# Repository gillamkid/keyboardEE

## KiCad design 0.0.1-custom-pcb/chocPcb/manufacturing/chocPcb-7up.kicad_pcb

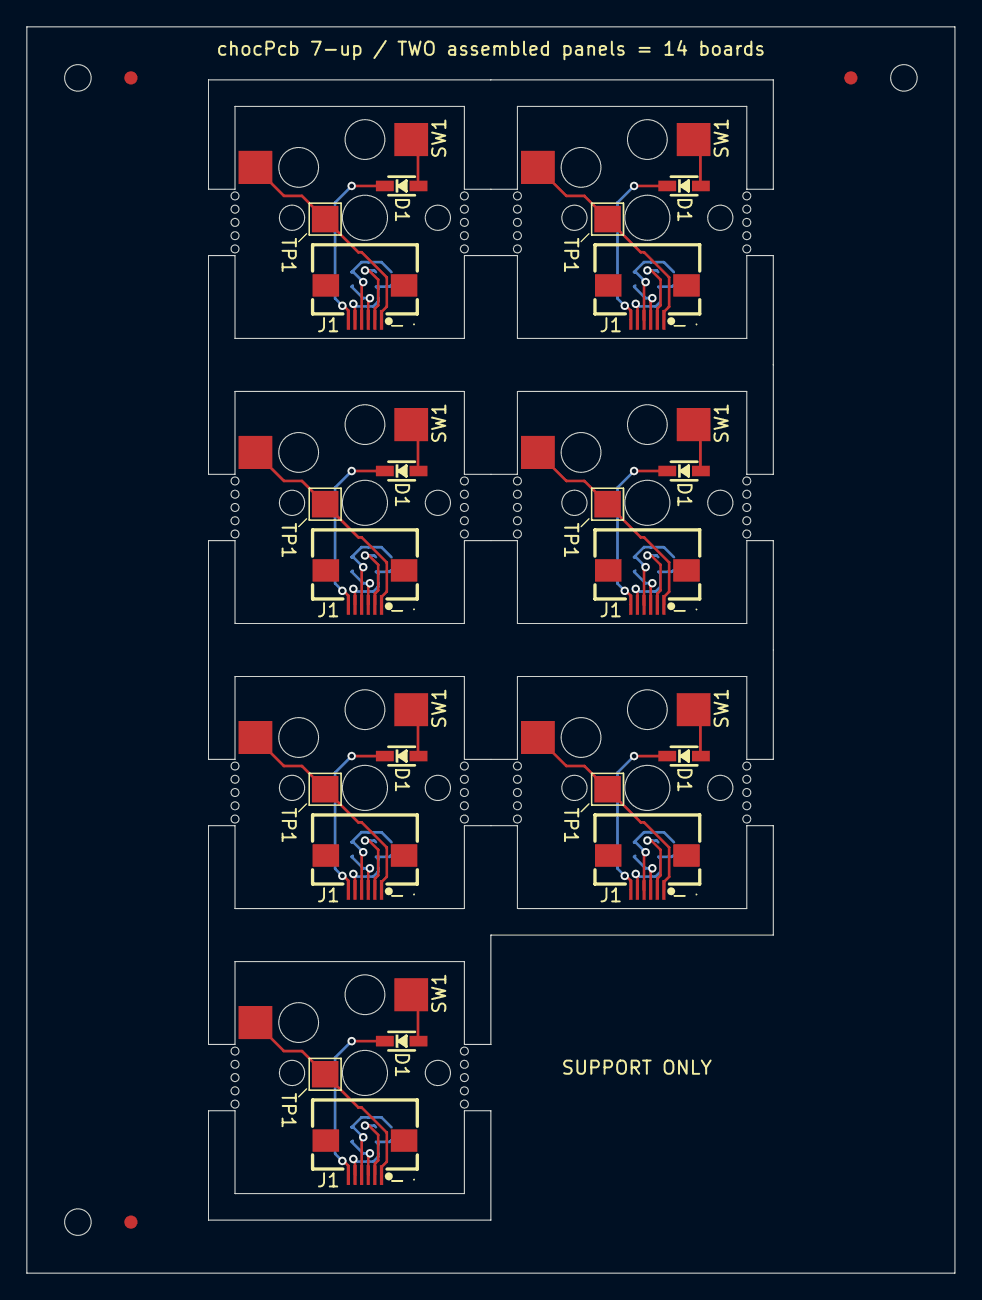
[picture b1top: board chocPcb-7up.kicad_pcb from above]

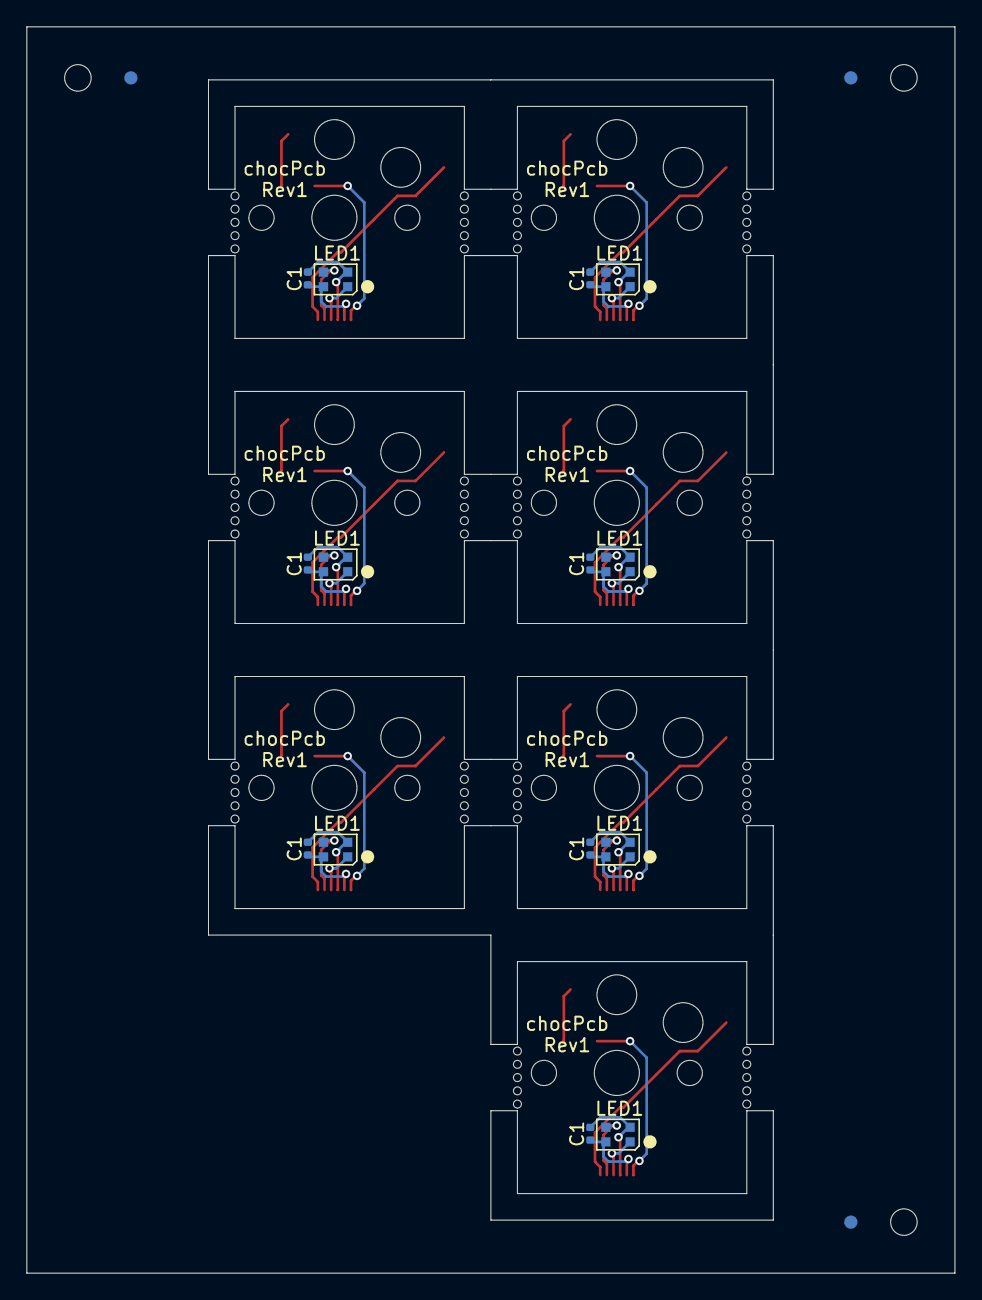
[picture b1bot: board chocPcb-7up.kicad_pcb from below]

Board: 2 copper layers, 70.0 x 94.0 mm, 121 parts (17 on the bottom side), 49 nets.

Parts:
C1_1, C1_2, C1_3, C1_4, C1_5, C1_6, C1_7: 100nF; C_0402_1005Metric
D1_1, D1_2, D1_3, D1_4, D1_5, D1_6, D1_7: 1N4148WS; SOD-323
FIDB1, FIDB2, FIDB3: Fiducial; Fiducial_1mm_B
FIDF1, FIDF2, FIDF3: Fiducial; Fiducial_1mm_F
J1_1, J1_2, J1_3, J1_4, J1_5, J1_6, J1_7: HC-FPC-0.5-6P-FH20; FPC-SMD_6P-P0.50_HC-FPC-0.5-6P-FH20
LED1_1, LED1_2, LED1_3, LED1_4, LED1_5, LED1_6, LED1_7: WS2812B-2020; LED_WS2812B-2020_PLCC4_2.0x2.0mm
MB1L1, MB1L2, MB1L3, MB1L4, MB1L5, MB1R1, MB1R2, MB1R3, MB1R4, MB1R5, MB2L1, MB2L2, MB2L3, MB2L4, MB2L5, MB2R1, MB2R2, MB2R3, MB2R4, MB2R5, MB3L1, MB3L2, MB3L3, MB3L4, MB3L5, MB3R1, MB3R2, MB3R3, MB3R4, MB3R5, MB4L1, MB4L2, MB4L3, MB4L4, MB4L5, MB4R1, MB4R2, MB4R3, MB4R4, MB4R5, MB5L1, MB5L2, MB5L3, MB5L4, MB5L5, MB5R1, MB5R2, MB5R3, MB5R4, MB5R5, MB6L1, MB6L2, MB6L3, MB6L4, MB6L5, MB6R1, MB6R2, MB6R3, MB6R4, MB6R5, MB7L1, MB7L2, MB7L3, MB7L4, MB7L5, MB7R1, MB7R2, MB7R3, MB7R4, MB7R5: NPTH; NPTH_0.6
SW1_1, SW1_2, SW1_3, SW1_4, SW1_5, SW1_6, SW1_7: Kailh Choc socket; KAILH_CHOC_SOCKET
TOOL1, TOOL2, TOOL3: NPTH; NPTH_2.0
TP1_1, TP1_2, TP1_3, TP1_4, TP1_5, TP1_6, TP1_7: TestPoint_Pad_2.0x2.0mm

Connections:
B1/GND: C1_1.2, J1_1.4, LED1_1.2
B1/N$2: D1_1.A, SW1_1.1
B1/NEO_IN: J1_1.2, LED1_1.3
B1/NEO_OUT: J1_1.3, LED1_1.1
B1/SWITCHA: J1_1.1, SW1_1.2, TP1_1.1
B1/SWITCHC: D1_1.C, J1_1.6
B1/VDD: C1_1.1, J1_1.5, LED1_1.4
B2/GND: C1_2.2, J1_2.4, LED1_2.2
B2/N$2: D1_2.A, SW1_2.1
B2/NEO_IN: J1_2.2, LED1_2.3
B2/NEO_OUT: J1_2.3, LED1_2.1
B2/SWITCHA: J1_2.1, SW1_2.2, TP1_2.1
B2/SWITCHC: D1_2.C, J1_2.6
B2/VDD: C1_2.1, J1_2.5, LED1_2.4
B3/GND: C1_3.2, J1_3.4, LED1_3.2
B3/N$2: D1_3.A, SW1_3.1
B3/NEO_IN: J1_3.2, LED1_3.3
B3/NEO_OUT: J1_3.3, LED1_3.1
B3/SWITCHA: J1_3.1, SW1_3.2, TP1_3.1
B3/SWITCHC: D1_3.C, J1_3.6
B3/VDD: C1_3.1, J1_3.5, LED1_3.4
B4/GND: C1_4.2, J1_4.4, LED1_4.2
B4/N$2: D1_4.A, SW1_4.1
B4/NEO_IN: J1_4.2, LED1_4.3
B4/NEO_OUT: J1_4.3, LED1_4.1
B4/SWITCHA: J1_4.1, SW1_4.2, TP1_4.1
B4/SWITCHC: D1_4.C, J1_4.6
B4/VDD: C1_4.1, J1_4.5, LED1_4.4
B5/GND: C1_5.2, J1_5.4, LED1_5.2
B5/N$2: D1_5.A, SW1_5.1
B5/NEO_IN: J1_5.2, LED1_5.3
B5/NEO_OUT: J1_5.3, LED1_5.1
B5/SWITCHA: J1_5.1, SW1_5.2, TP1_5.1
B5/SWITCHC: D1_5.C, J1_5.6
B5/VDD: C1_5.1, J1_5.5, LED1_5.4
B6/GND: C1_6.2, J1_6.4, LED1_6.2
B6/N$2: D1_6.A, SW1_6.1
B6/NEO_IN: J1_6.2, LED1_6.3
B6/NEO_OUT: J1_6.3, LED1_6.1
B6/SWITCHA: J1_6.1, SW1_6.2, TP1_6.1
B6/SWITCHC: D1_6.C, J1_6.6
B6/VDD: C1_6.1, J1_6.5, LED1_6.4
B7/GND: C1_7.2, J1_7.4, LED1_7.2
B7/N$2: D1_7.A, SW1_7.1
B7/NEO_IN: J1_7.2, LED1_7.3
B7/NEO_OUT: J1_7.3, LED1_7.1
B7/SWITCHA: J1_7.1, SW1_7.2, TP1_7.1
B7/SWITCHC: D1_7.C, J1_7.6
B7/VDD: C1_7.1, J1_7.5, LED1_7.4

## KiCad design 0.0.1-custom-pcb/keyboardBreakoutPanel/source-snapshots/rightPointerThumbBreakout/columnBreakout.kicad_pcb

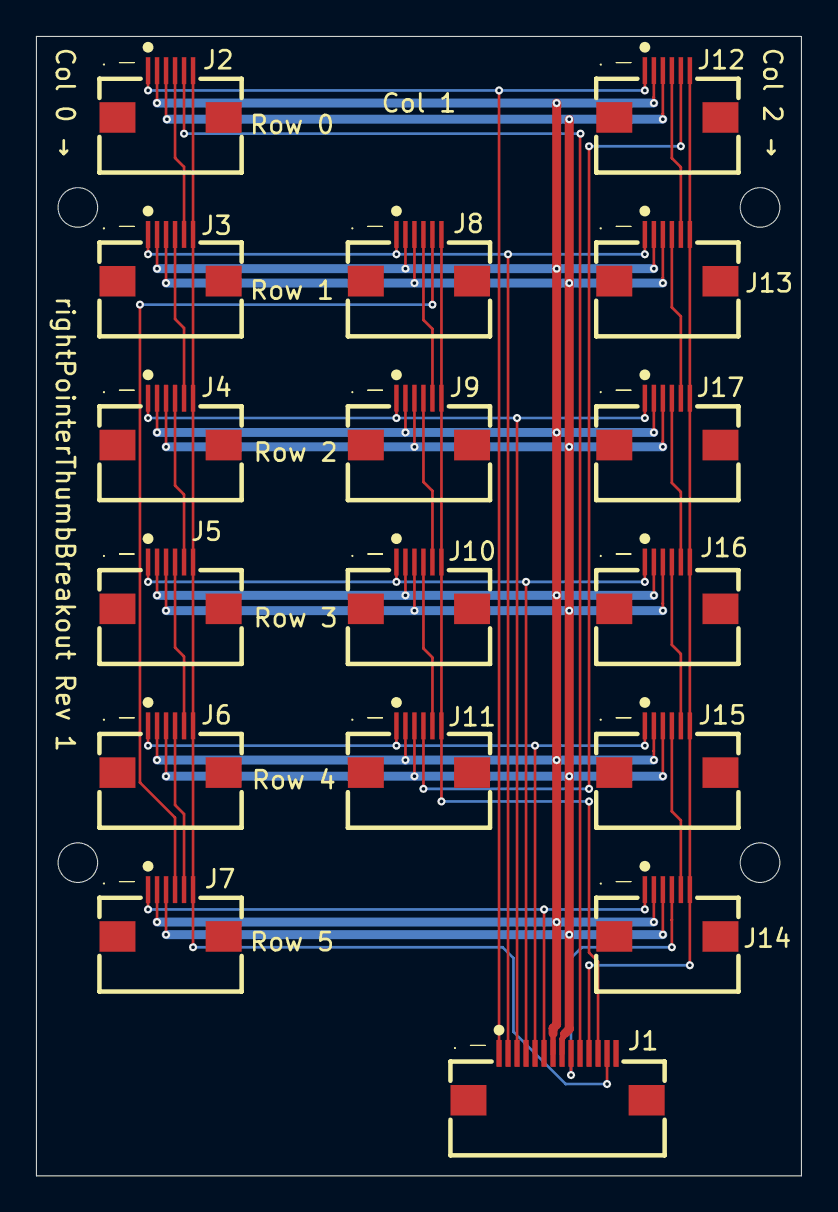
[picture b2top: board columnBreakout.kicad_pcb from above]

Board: 2 copper layers, 42.5 x 63.3 mm, 21 parts (0 on the bottom side), 28 nets.

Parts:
H1, H2, H3, H4: MountingHole_2.2mm_M2_4.4mmHead
J1: HC-FPC-0.5-14P-FH20; FPC-SMD_14P-P0.50_HC-FPC-0.5-14P-FH20
J2, J3, J4, J5, J6, J7, J8, J9, J10, J11, J12, J13, J14, J15, J16, J17: HC-FPC-0.5-6P-FH20; FPC-SMD_6P-P0.50_HC-FPC-0.5-6P-FH20

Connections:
/C0: J1.13, J2.6, J3.6, J4.6, J5.6, J6.6, J7.6
/C1: J1.12, J8.6, J9.6, J10.6, J11.6
/C2: J1.11, J12.6, J13.6, J14.6, J15.6, J16.6, J17.6
/GND: J1.8, J2.3, J3.3, J4.3, J5.3, J6.3, J7.3, J8.3, J9.3, J10.3, J11.3, J12.3, J13.3, J14.3, J15.3, J16.3, J17.3
/IN0: J1.10, J2.5
/IN1: J2.4, J3.5
/IN2: J3.4, J4.5
/IN3: J4.4, J5.5
/IN4: J5.4, J6.5
/IN5: J6.4, J7.5
/IN6: J7.4, J8.5
/IN7: J8.4, J9.5
/IN8: J9.4, J10.5
/IN9: J10.4, J11.5
/IN10: J11.4, J12.5
/IN11: J12.4, J13.5
/IN12: J13.4, J17.5
/IN13: J16.5, J17.4
/IN14: J15.5, J16.4
/IN15: J14.5, J15.4
/IN16: J1.9, J14.4
/R0: J1.1, J2.1, J12.1
/R1: J1.2, J3.1, J8.1, J13.1
/R2: J1.3, J4.1, J9.1, J17.1
/R3: J1.4, J5.1, J10.1, J16.1
/R4: J1.5, J6.1, J11.1, J15.1
/R5: J1.6, J7.1, J14.1
/VDD: J1.7, J2.2, J3.2, J4.2, J5.2, J6.2, J7.2, J8.2, J9.2, J10.2, J11.2, J12.2, J13.2, J14.2, J15.2, J16.2, J17.2
